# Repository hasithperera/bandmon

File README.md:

# bandmon

This is a project intended to deploy a distributed band monitoring system to better quantify 2m repeater usage. 

The goal was to implement a system that can monitor a repeater audio output and detect activity and generate a summary to evaluate activity. 

funding provided by the WVU Amateur radio club [W8CUL](https://wvuarc.orgs.wvu.edu)
## Dependencies 

- Arduino board manager: `http://arduino.esp8266.com/stable/package_esp8266com_index.json`
- MQTT pub/sub library placed in side `~/Arduino/libraries/` 

```
git clone git@github.com:knolleary/pubsubclient.git
```
- this can also be added using the library manager
- more info[link](https://pubsubclient.knolleary.net)

## Tools 

- [Mqtt_spy](https://github.com/eclipse/paho.mqtt-spy/releases/) > 1.0.1-beta9. Running with jre 8.6 works well in linux/Windows. 
	- MAC still has trouble running it correctly
- [esp_tools](https://github.com/espressif/esptool) - For installation and firmware update

## To-do list

- [x] Basic code for Wifi and MQTT connection
- [x] Send repeater activity based on audio input
 - [x] EEPROM data save
- [ ] Configurable settings TUI
- [ ] Hardware design 
    - [ ] final PCB design - audio based
    - [ ] 3D printable case design
- [x] Server end logging
	- [x] Display with Grafana
	- [x] Deploy in the ARC server
- [ ] Write an article about it 
    - [ ] reach out to other local clubs

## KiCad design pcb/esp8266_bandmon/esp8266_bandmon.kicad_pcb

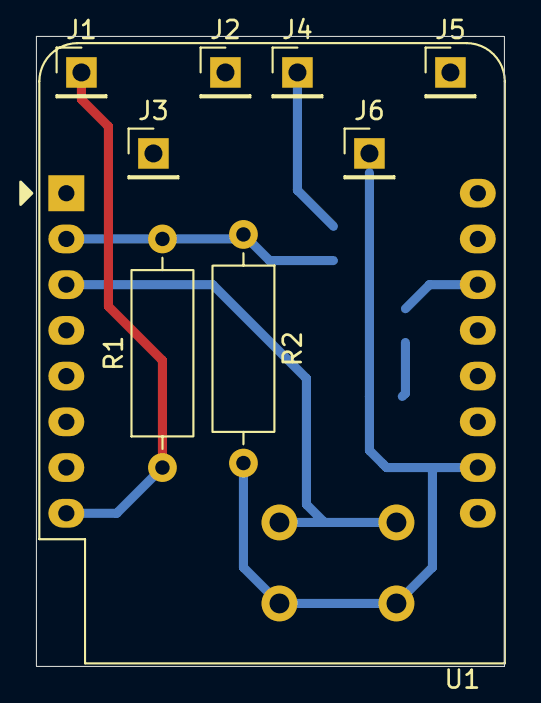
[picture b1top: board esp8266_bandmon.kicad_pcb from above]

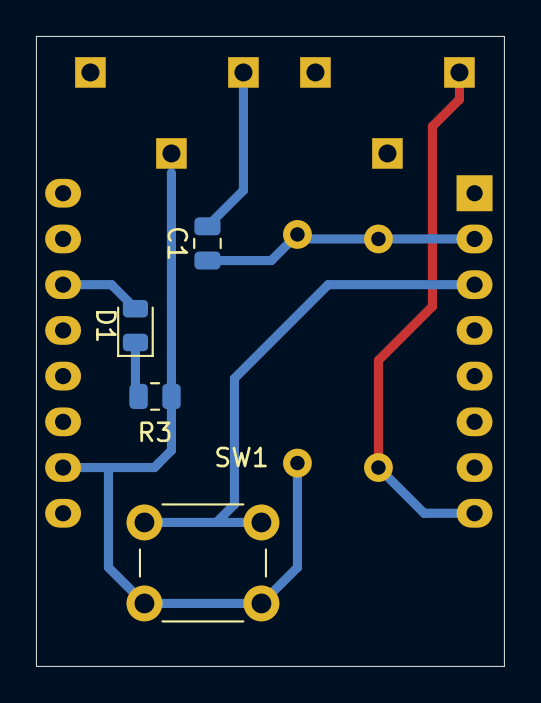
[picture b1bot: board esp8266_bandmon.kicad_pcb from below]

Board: 2 copper layers, 26.0 x 35.0 mm, 13 parts (4 on the bottom side), 7 nets.

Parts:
C1: .1uf; C_0805_2012Metric
D1: LED; LED_0805_2012Metric
J1: tip-3.5; PinHeader_1x01_P2.54mm_Vertical
J2, J5: center; PinHeader_1x01_P2.54mm_Vertical
J3, J6: ring; PinHeader_1x01_P2.54mm_Vertical
J4: tip-2.5; PinHeader_1x01_P2.54mm_Vertical
R1, R2: 10k; R_Axial_DIN0309_L9.0mm_D3.2mm_P12.70mm_Horizontal
R3: 330; R_0805_2012Metric
SW1: reset_wifi; SW_PUSH_6mm
U1: WEMOS_D1_mini; WEMOS_D1_mini_light

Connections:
GND: J6.1, R2.2, R3.2, SW1.2, U1.10 (GND)
unnamed: D1.2 (A), U1.14 (SCL/D1)
unnamed: D1.1 (K), R3.1
unnamed: J1.1, R1.1, U1.8 (3V3)
unnamed: C1.2, J4.1
unnamed: C1.1, R1.2, R2.1, U1.2 (A0)
unnamed: SW1.1, U1.3 (D0)

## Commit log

2024-11-29 added old files from gitlab
2024-11-30 Added fixes to the new firmware and basic functions working
2024-11-30 adding a working telegraf config to save data to influxdb2
2024-11-30 deployable 0.1v
2024-12-02 added Grafana config
2024-12-02 updated the read me with docker deployment commands
2025-05-03 modified the voice detection algorithm and added auto noise level calibration at restart
2025-07-03 added wifimanager basics
2025-07-03 updated voice detection and noise calibration code
2025-07-04 working wifimanager
2025-07-04 removed unused code and comments
2025-07-05 added a PCB v1(3.3V)
2025-07-08 added mqtt debug functions and restart functions
2025-07-08 working sub commands. removed global commands
2025-07-17 updated the mqtt cmd topic
2025-09-09 added changes to make wifi setup better and non-blocking
